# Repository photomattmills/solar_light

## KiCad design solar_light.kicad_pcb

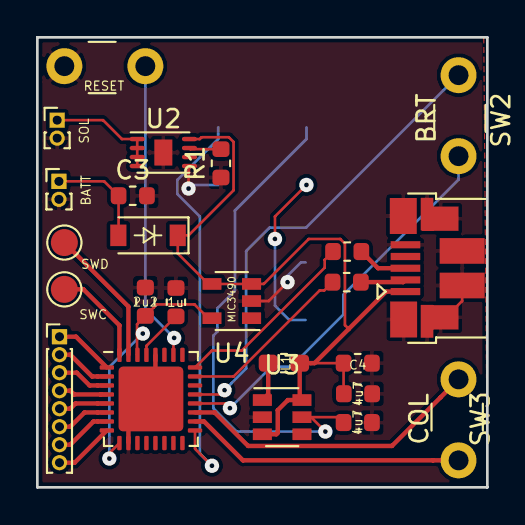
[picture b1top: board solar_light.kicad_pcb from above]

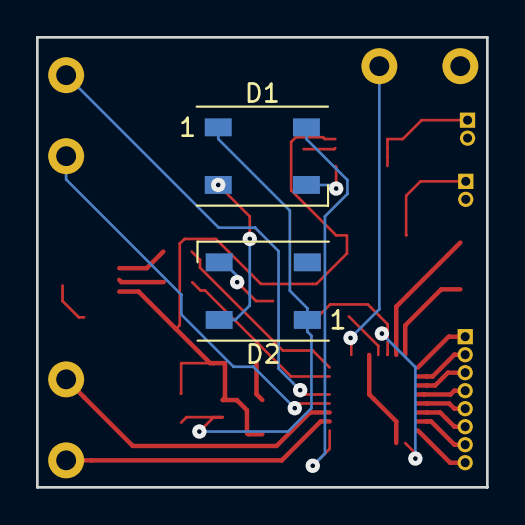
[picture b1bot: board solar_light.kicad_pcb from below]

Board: 2 copper layers, 25.0 x 25.0 mm, 25 parts (2 on the bottom side), 28 nets.

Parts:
C1, C4: 1u; C_0603_1608Metric
C2, C6: 4u7; C_0603_1608Metric
C3: C_Small; C_0603_1608Metric
C5: 2u2; C_0603_1608Metric
D1, D2: WS2812B; LED_WS2812B_PLCC4_5.0x5.0mm_P3.2mm
D3: D_Schottky_Small; D_SOD-123
J1: SOL; PinHeader_1x02_P1.00mm_Vertical
J2: BATT; PinHeader_1x02_P1.00mm_Vertical
J3: breakout header; PinHeader_1x08_P1.00mm_Vertical
J4: USB_B_Mini; USB_Micro-B_Amphenol_10103594-0001LF_Horizontal-no-th
L1: 4.7uH; R_0603_1608Metric_Pad1.05x0.95mm_HandSolder
R1, R2: R_Small; R_0603_1608Metric
SW1: RESET; SW_PUSH_3.5mm
SW2: BRT; SW_PUSH_3.5mm
SW3: COL; SW_PUSH_3.5mm
TP1: SWC; TestPoint_Pad_D1.5mm
TP2: SWD; TestPoint_Pad_D1.5mm
U1: ATSAMD21E18A-MU; QFN-32-1EP_5x5mm_P0.5mm_EP3.6x3.6mm
U2: MC34673; TDFN-8-2x3-NXP
U3: ISL9111; SOT-23-6
U4: MIC3490; SOT-23-5

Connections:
/3v3: C5.1, U1.9, U1.30, U4.5
/5v: C2.1, D1.1, D2.1, U3.5
/D+: R2.1, U1.24
/Solar+: J1.1, U2.1, U2.2, U2.3, U2.4
/light: D1.4, U1.17
GND: C1.2, C2.2, C3.2, C4.2, C5.2, C6.2, D1.3, D2.3, J1.2, J2.2, J4.5, J4.6, R1.1, SW1.1, U1.10, U1.28, U1.33, U2.5, U2.9, U3.2, U4.2
unnamed: C1.1, U1.29
unnamed: C3.1, D3.2, J2.1
unnamed: D1.2, D2.4
unnamed: J3.1, U1.1
unnamed: J3.2, U1.2
unnamed: J3.3, U1.3
unnamed: J3.4, U1.4
unnamed: J3.5, U1.5
unnamed: J3.6, U1.6
unnamed: J3.7, U1.7
unnamed: J3.8, U1.8
unnamed: J4.3, R2.2
unnamed: L1.1, U3.1
unnamed: R1.2, U2.7
unnamed: SW1.2, U1.26
unnamed: SW2.1, U1.20
unnamed: SW2.2, U1.21
unnamed: SW3.1, U1.19
unnamed: SW3.2, U1.18
unnamed: TP1.1, U1.32
unnamed: TP2.1, U1.31
VCC: C4.1, C6.1, D3.1, J4.1, L1.2, U2.8, U3.3, U3.6, U4.3, U4.4

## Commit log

2019-04-22 schematice mostly complete
2019-04-23 schematic done; pcb started
2019-04-24 routed!
